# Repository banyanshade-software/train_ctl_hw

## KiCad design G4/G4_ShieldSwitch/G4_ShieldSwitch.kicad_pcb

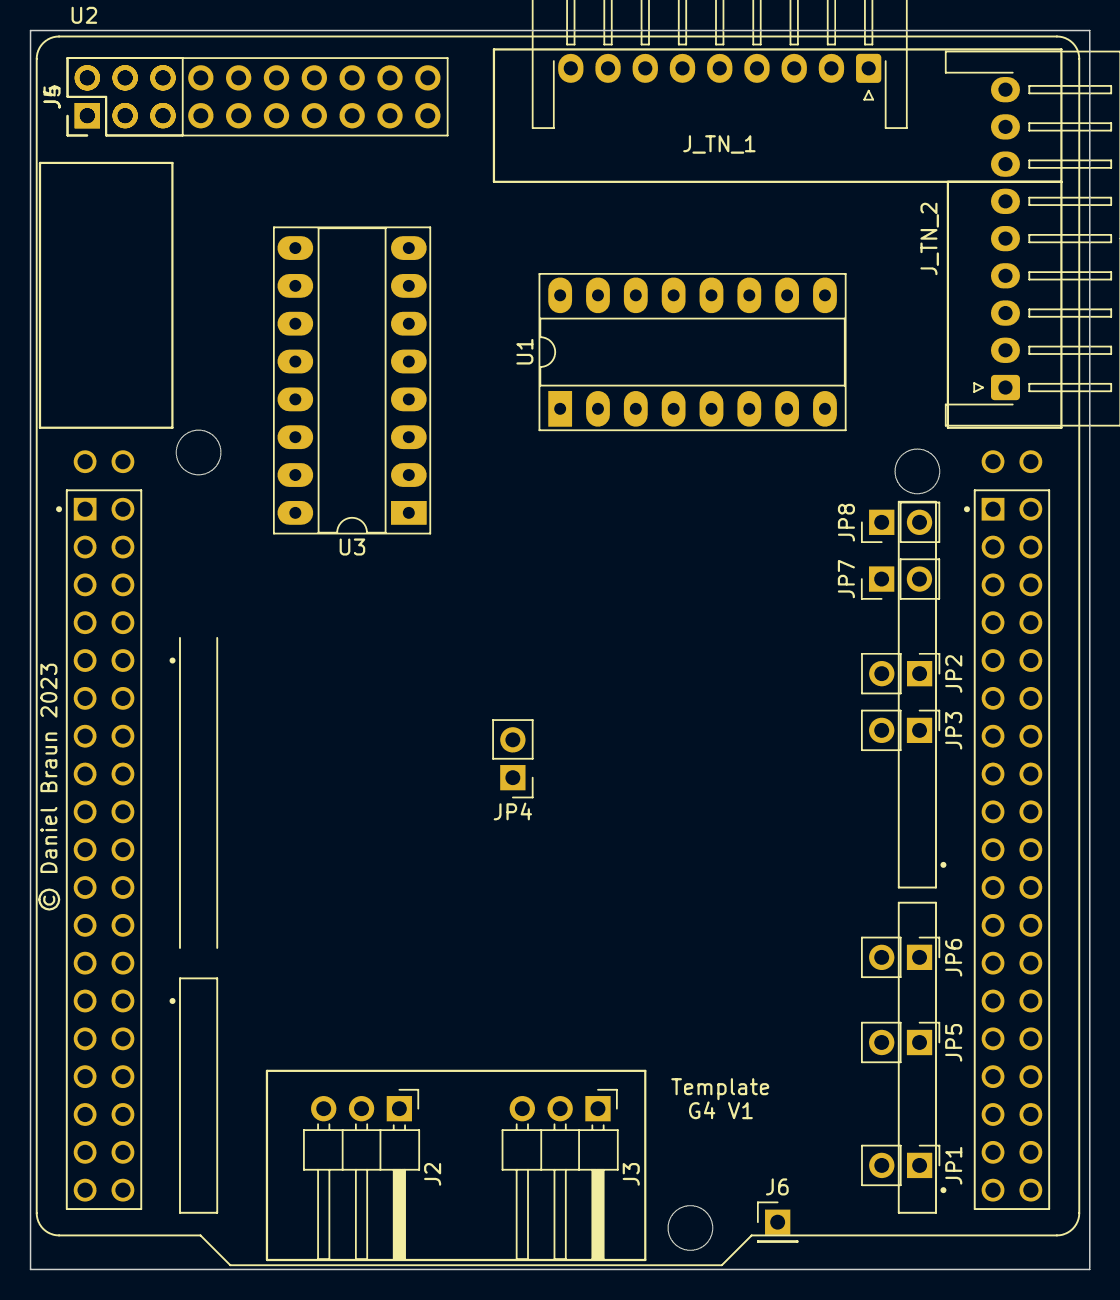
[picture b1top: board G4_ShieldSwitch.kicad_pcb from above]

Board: 2 copper layers, 71.1 x 83.2 mm, 18 parts (0 on the bottom side), 35 nets, no tracks yet.

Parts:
J2, J3: Conn_01x03_Male; PinHeader_1x03_P2.54mm_Horizontal
J4: Conn_02x10_Odd_Even; PinHeader_2x10_P2.54mm_Vertical
J5: Conn_02x03_Odd_Even; PinHeader_2x03_P2.54mm_Vertical
J6: Conn_01x01_Female; PinHeader_1x01_P2.54mm_Vertical
JP1, JP2, JP3, JP4, JP5, JP6, JP7, JP8: SJ; PinHeader_1x02_P2.54mm_Vertical
J_TN_1, J_TN_2: Conn_01x09_Female; JST_XH_S9B-XH-A-1_1x09_P2.50mm_Horizontal
U1, U3: ULN2003A; DIP-16_W7.62mm_Socket_LongPads
U2: NUCLEO-G491RE; MODULE_NUCLEO-G491RE20

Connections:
5V: J4.1, J5.1
12V: J4.5, J5.5
+12V: J_TN_1.2, J_TN_1.5, J_TN_1.8, J_TN_2.2, J_TN_2.5, J_TN_2.8, U1.9 (COM), U3.9 (COM)
ALED8: J_TN_1.7, U3.12 (O5)
ALED9: J_TN_1.9, U3.11 (O6)
GND: J4.3, J5.3, J6.1, U1.8 (GND), U2.CN7_8 (CN7_GND), U2.CN7_19 (CN7_GND), U2.CN7_20 (CN7_GND), U2.CN7_22 (CN7_GND), U2.CN10_9 (CN10_GND), U2.CN10_20 (CN10_GND), U3.8 (GND)
unnamed: J_TN_1.1, U3.16 (O1)
unnamed: J_TN_1.3, U3.15 (O2)
unnamed: J_TN_1.4, U3.14 (O3)
unnamed: J_TN_1.6, U3.13 (O4)
unnamed: J_TN_2.1, U1.16 (O1)
unnamed: J_TN_2.3, U1.15 (O2)
unnamed: J_TN_2.4, U1.14 (O3)
unnamed: J_TN_2.6, U1.13 (O4)
unnamed: J_TN_2.7, U1.12 (O5)
unnamed: J_TN_2.9, U1.11 (O6)
unnamed: JP8.2 (B), U2.CN10_1 (PC9)
unnamed: JP7.2 (B), U2.CN10_2 (PC8)
unnamed: JP2.1 (A), U2.CN10_11 (PA5)
unnamed: JP3.1 (A), U2.CN10_13 (PA6)
unnamed: JP6.1 (A), U2.CN10_25 (PB10)
unnamed: JP5.1 (A), U2.CN10_29 (PB5)
unnamed: JP1.1 (A), U2.CN10_37 (PA3)
TN0A: U1.1 (I1), U2.CN10_3 (PB8/CAN1RX)
TN0B: U1.2 (I2), U2.CN10_6 (PC5)
TN1A: U1.3 (I3), U2.CN10_19 (PC7)
TN1B: U1.4 (I4), U2.CN10_28 (PB14)
TN2A: JP1.2 (B), JP7.1 (A), U1.5 (I5)
TN2B: U1.6 (I6), U2.CN10_34 (PC4)
TN3A: JP4.2 (B), U3.1 (I1)
TN3B: JP6.2 (B), U3.2 (I2)
TN4A: JP8.1 (A), U3.3 (I3)
TN4B: JP2.2 (B), U3.4 (I4)
TN5A: JP3.2 (B), U3.5 (I5)
TN5B: JP5.2 (B), U3.6 (I6)

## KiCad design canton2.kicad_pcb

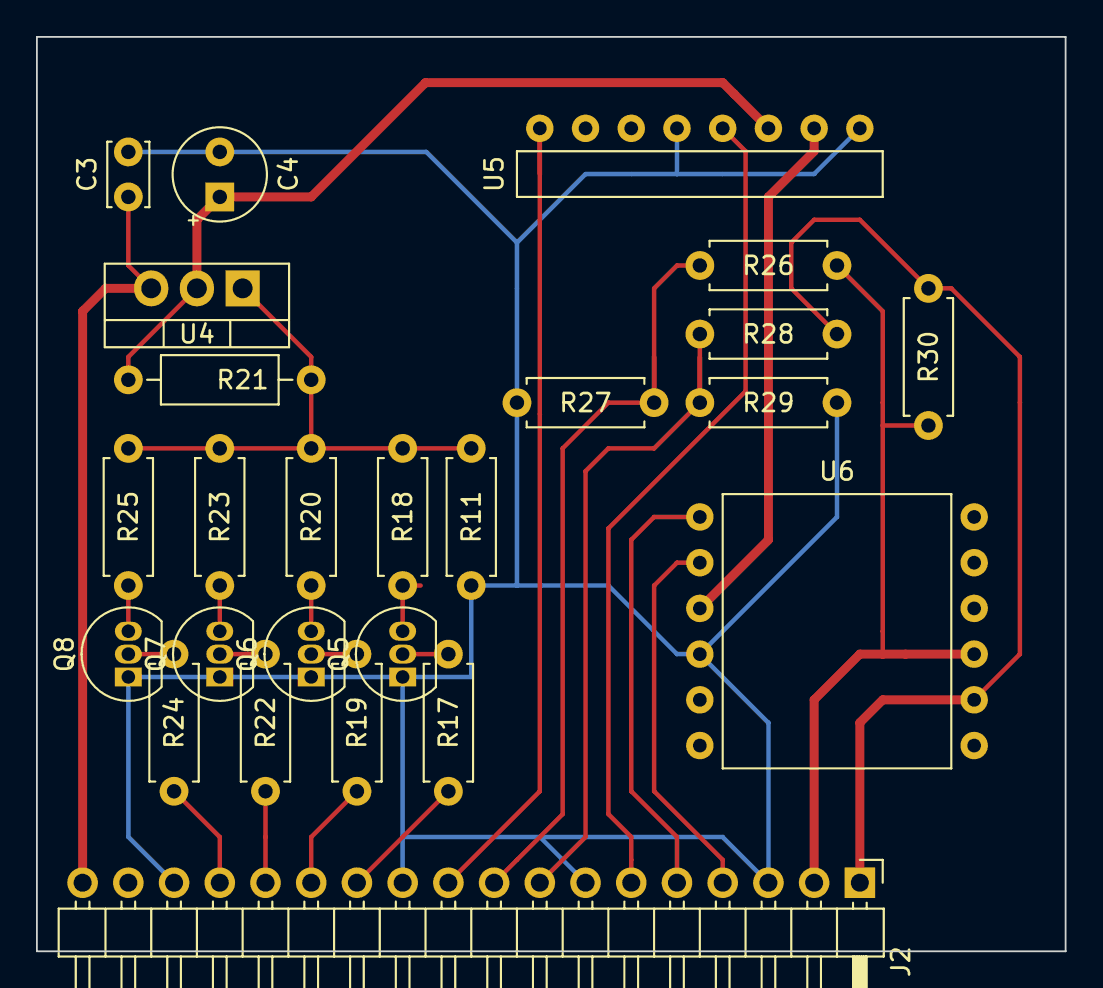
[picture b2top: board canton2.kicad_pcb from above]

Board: 2 copper layers, 57.2 x 50.8 mm, 25 parts (0 on the bottom side), 25 nets.

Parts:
C3: 0.1µF; C_Disc_D3.4mm_W2.1mm_P2.50mm
C4: 10µF; CP_Radial_Tantal_D5.0mm_P2.50mm
J2: Conn_01x18; PinHeader_1x18_P2.54mm_Horizontal
Q5, Q6, Q7, Q8: PN2222A; TO-92_Inline
R11, R18, R20, R23, R25: R; R_Axial_DIN0207_L6.3mm_D2.5mm_P7.62mm_Horizontal
R17, R19, R22, R24, R27, R29: 2200; R_Axial_DIN0207_L6.3mm_D2.5mm_P7.62mm_Horizontal
R21: 240; R_Axial_DIN0207_L6.3mm_D2.5mm_P10.16mm_Horizontal
R26, R28: 10k; R_Axial_DIN0207_L6.3mm_D2.5mm_P7.62mm_Horizontal
R30: 3k; R_Axial_DIN0207_L6.3mm_D2.5mm_P7.62mm_Horizontal
U4: LM317_TO220; TO-220-3_Vertical
U5: CJMCU-4080; module_1x8
U6: ModuleDRV8833; module_2x6

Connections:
3.3V: J2.6, U5.4
12Vunreg: C3.1, J2.18, U4.3
CT0: J2.12, R17.2
CT1: J2.13, R19.2
CT2: J2.14, R22.2
CT3: J2.15, R24.2
GND: C3.2, C4.2, J2.3, J2.7, J2.11, J2.16, Q5.1, Q6.1, Q7.1, Q8.1, R11.2, R27.2, R29.2, U5.1, U5.5, U6.10
ISENSE: J2.10, U5.8
unnamed: C4.1, R21.1, U4.2, U5.3
unnamed: Q5.2, R17.1
unnamed: Q5.3, R18.2
unnamed: Q6.2, R19.1
unnamed: Q6.3, R20.2
unnamed: Q7.2, R22.1
unnamed: Q7.3, R23.2
unnamed: Q8.2, R24.1
unnamed: Q8.3, R25.2
unnamed: R11.1, R18.1, R20.1, R21.2, R23.1, R25.1, U4.1
unnamed: U5.2, U6.9
PWM1: J2.5, U6.7
PWM2: J2.4, U6.8
TRACK0: J2.1, R28.1, R30.1, U6.2
TRACK1: J2.2, R26.1, R30.2, U6.3
VSENSE0: J2.9, R26.2, R27.1
VSENSE1: J2.8, R28.2, R29.1

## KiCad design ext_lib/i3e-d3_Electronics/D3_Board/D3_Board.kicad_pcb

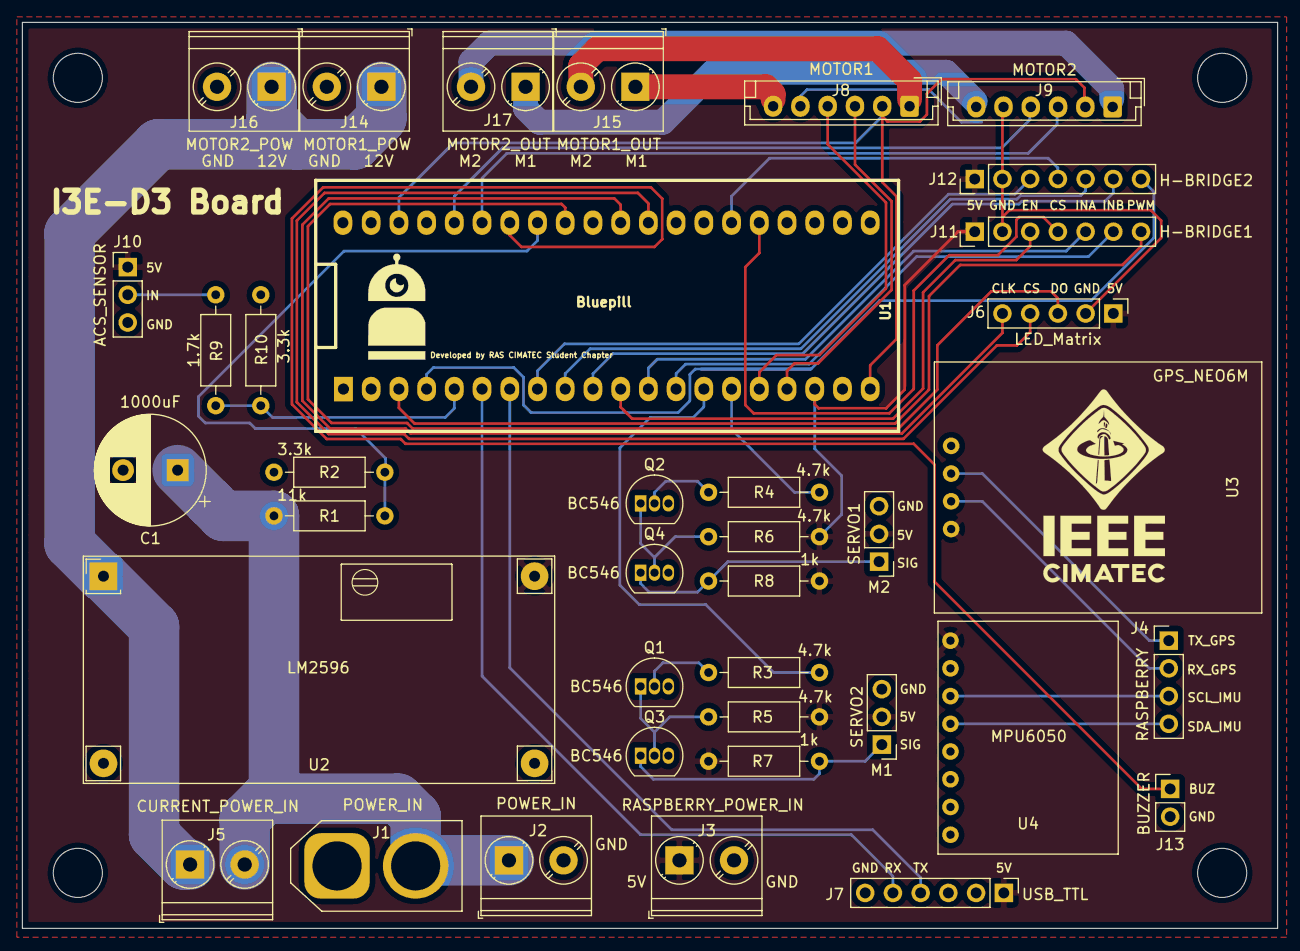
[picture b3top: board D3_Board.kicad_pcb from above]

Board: 2 copper layers, 115.0 x 83.0 mm, 38 parts (0 on the bottom side), 44 nets.

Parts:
C1: 1000uF; CP_Radial_D10.0mm_P5.00mm
J1: POWER_IN; AMASS_XT60-M_1x02_P7.20mm_Vertical
J2: POWER_IN; TerminalBlock_Phoenix_PT-1,5-2-5.0-H_1x02_P5.00mm_Horizontal
J3: RASPBERRY_POWER_IN; TerminalBlock_Phoenix_PT-1,5-2-5.0-H_1x02_P5.00mm_Horizontal
J4: RASPBERRY; PinHeader_1x04_P2.54mm_Vertical
J5: CURRENT_POWER_IN; TerminalBlock_Phoenix_PT-1,5-2-5.0-H_1x02_P5.00mm_Horizontal
J6: LED_Matrix; PinHeader_1x05_P2.54mm_Vertical
J7: USB_TTL; PinHeader_1x06_P2.54mm_Vertical
J8: MOTOR1; JST_EH_B6B-EH-A_1x06_P2.50mm_Vertical
J9: MOTOR2; JST_EH_B6B-EH-A_1x06_P2.50mm_Vertical
J10: ACS_SENSOR; PinHeader_1x03_P2.54mm_Vertical
J11: H-BRIDGE1; PinHeader_1x07_P2.54mm_Vertical
J12: H-BRIDGE2; PinHeader_1x07_P2.54mm_Vertical
J13: BUZZER; PinHeader_1x02_P2.54mm_Vertical
J14: MOTOR1_POW; TerminalBlock_Phoenix_PT-1,5-2-5.0-H_1x02_P5.00mm_Horizontal
J15: MOTOR1_OUT; TerminalBlock_Phoenix_PT-1,5-2-5.0-H_1x02_P5.00mm_Horizontal
J16: MOTOR2_POW; TerminalBlock_Phoenix_PT-1,5-2-5.0-H_1x02_P5.00mm_Horizontal
J17: MOTOR2_OUT; TerminalBlock_Phoenix_PT-1,5-2-5.0-H_1x02_P5.00mm_Horizontal
M1: SERVO2; PinHeader_1x03_P2.54mm_Vertical
M2: SERVO1; PinHeader_1x03_P2.54mm_Vertical
Q1, Q2, Q3, Q4: BC546; TO-92_Inline
R1: 11k; R_Axial_DIN0207_L6.3mm_D2.5mm_P10.16mm_Horizontal
R2, R10: 3.3k; R_Axial_DIN0207_L6.3mm_D2.5mm_P10.16mm_Horizontal
R3, R4, R5, R6: 4.7k; R_Axial_DIN0207_L6.3mm_D2.5mm_P10.16mm_Horizontal
R7, R8: 1k; R_Axial_DIN0207_L6.3mm_D2.5mm_P10.16mm_Horizontal
R9: 1.7k; R_Axial_DIN0207_L6.3mm_D2.5mm_P10.16mm_Horizontal
U1: Bluepill; BluePill_STM32F103C
U2: LM2596; LM2596_module
U3: GPS_NEO6M; GPS_NEO6M_module
U4: MPU6050; MPU6050_module

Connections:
+3V3: J8.2, J9.2, U1.20, U1.38
+5V: J3.1, J6.1, J7.1, J10.1, J11.1, J12.1, M1.2, M2.2, R5.2, R6.2, R7.2, R8.2, U1.18, U2.4, U3.1, U4.1
+12V: J5.1, J14.1, J16.1, U2.1
/ACS: R9.2, R10.1, U1.5
/AVS: R1.2, R2.1, U1.33
/BUZZER: J13.1, U1.34
/CLK_LED: J6.5, U1.30
/CS_LED: J6.4, U1.29
/DOUT_LED: J6.3, U1.32
/ENCODER1_A: J8.4, U1.16
/ENCODER1_B: J8.3, U1.17
/ENCODER2_A: J9.4, U1.36
/ENCODER2_B: J9.3, U1.35
/MOTOR1_CS: J11.4, U1.25
/MOTOR1_EN: J11.3, U1.11
/MOTOR1_INA: J11.5, U1.12
/MOTOR1_INB: J11.6, U1.13
/MOTOR1_M1: J8.6, J15.1
/MOTOR1_M2: J8.1, J15.2
/MOTOR1_PWM: J11.7, U1.3
/MOTOR2_CS: J12.4, U1.26
/MOTOR2_EN: J12.3, U1.8
/MOTOR2_INA: J12.5, U1.9
/MOTOR2_INB: J12.6, U1.10
/MOTOR2_M1: J9.6, J17.1
/MOTOR2_M2: J9.1, J17.2
/MOTOR2_PWM: J12.7, U1.4
/RX_GPS: J4.2, U3.2
/RX_SERIAL: J7.5, U1.6
/SCL: J4.3, U4.3
/SDA: J4.4, U4.4
/SERVO1: R3.2, U1.14
/SERVO2: R4.2, U1.15
/TX_GPS: J4.1, U3.3
/TX_SERIAL: J7.4, U1.7
GND: C1.2, J1.1, J2.2, J3.2, J6.2, J7.6, J8.5, J9.5, J10.3, J11.2, J12.2, J13.2, J14.2, J16.2, M1.3, M2.3, Q1.3, Q2.3, Q3.3, Q4.3, R2.2, R10.2, U1.19, U1.39, U1.40, U2.2, U2.3, U3.4, U4.2
unnamed: C1.1, J1.2, J2.1, J5.2, R1.1
unnamed: J10.2, R9.1
unnamed: M1.1, Q3.1, R7.1
unnamed: M2.1, Q4.1, R8.1
unnamed: Q1.1, Q3.2, R5.1
unnamed: Q1.2, R3.1
unnamed: Q2.1, Q4.2, R6.1
unnamed: Q2.2, R4.1

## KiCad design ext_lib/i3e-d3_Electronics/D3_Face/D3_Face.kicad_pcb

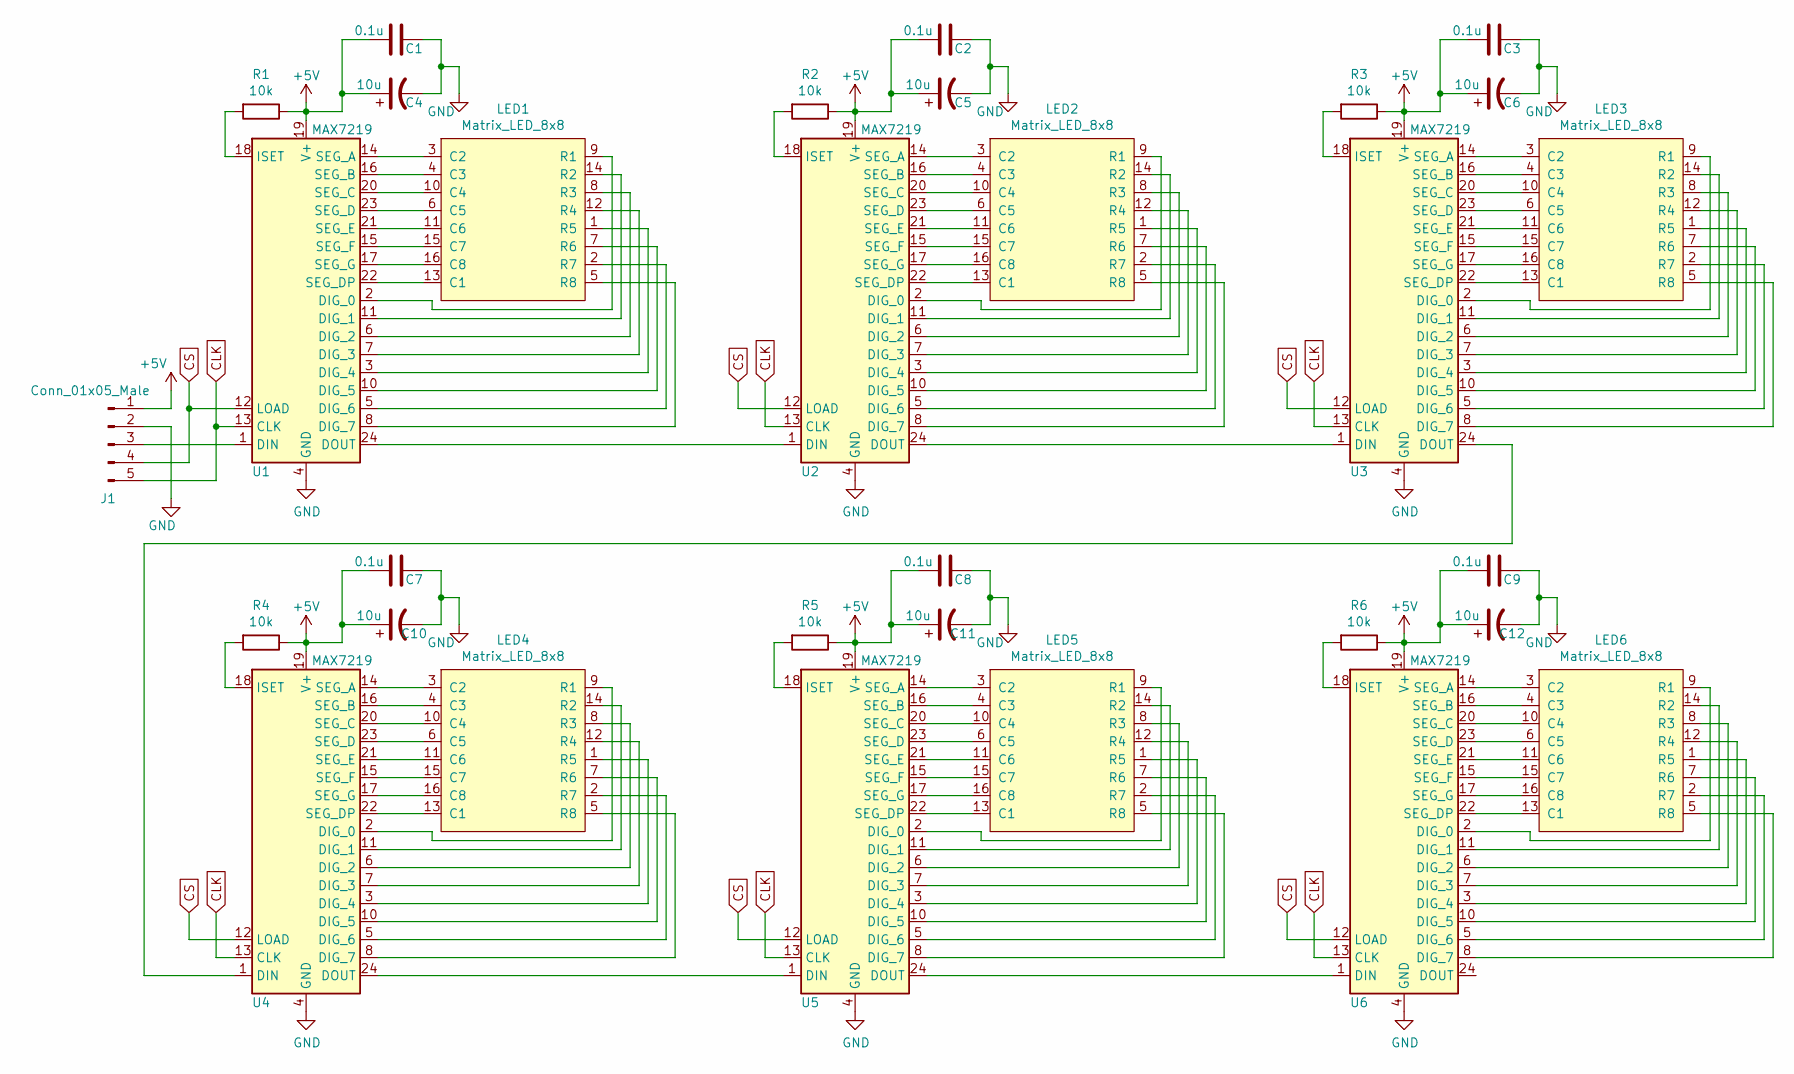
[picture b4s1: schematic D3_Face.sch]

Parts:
C1, C2, C3, C7, C8, C9: 0.1u; C_Disc_D4.3mm_W1.9mm_P5.00mm
C4, C5, C6, C10, C11, C12: 10u; CP_Radial_D4.0mm_P2.00mm
J1: Conn_01x05_Male; PinHeader_1x05_P2.54mm_Horizontal
LED1, LED2, LED3, LED4, LED5, LED6: Matrix_LED_8x8
R1, R2, R3, R4, R5, R6: 10k; R_Axial_DIN0207_L6.3mm_D2.5mm_P10.16mm_Horizontal
U1, U2, U3, U4, U5, U6: MAX7219; DIP-24_W7.62mm_Socket_LongPads

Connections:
+5V: C1.2, C2.2, C3.2, C4.1, C5.1, C6.1, C7.2, C8.2, C9.2, C10.1, C11.1, C12.1, J1.1, R1.1, R2.1, R3.1, R4.1, R5.1, R6.1, U1.19 (V+), U2.19 (V+), U3.19 (V+), U4.19 (V+), U5.19 (V+), U6.19 (V+)
CLK: J1.5, U1.13 (CLK), U2.13 (CLK), U3.13 (CLK), U4.13 (CLK), U5.13 (CLK), U6.13 (CLK)
CS: J1.4, U1.12 (LOAD), U2.12 (LOAD), U3.12 (LOAD), U4.12 (LOAD), U5.12 (LOAD), U6.12 (LOAD)
GND: C1.1, C2.1, C3.1, C4.2, C5.2, C6.2, C7.1, C8.1, C9.1, C10.2, C11.2, C12.2, J1.2, U1.4 (GND), U1.9 (GND), U2.4 (GND), U2.9 (GND), U3.4 (GND), U3.9 (GND), U4.4 (GND), U4.9 (GND), U5.4 (GND), U5.9 (GND), U6.4 (GND), U6.9 (GND)
unnamed: J1.3, U1.1 (DIN)
unnamed: LED1.1 (R5), U1.3 (DIG_4)
unnamed: LED1.2 (R7), U1.5 (DIG_6)
unnamed: LED1.3 (C2), U1.14 (SEG_A)
unnamed: LED1.4 (C3), U1.16 (SEG_B)
unnamed: LED1.5 (R8), U1.8 (DIG_7)
unnamed: LED1.6 (C5), U1.23 (SEG_D)
unnamed: LED1.7 (R6), U1.10 (DIG_5)
unnamed: LED1.8 (R3), U1.6 (DIG_2)
unnamed: LED1.9 (R1), U1.2 (DIG_0)
unnamed: LED1.10 (C4), U1.20 (SEG_C)
unnamed: LED1.11 (C6), U1.21 (SEG_E)
unnamed: LED1.12 (R4), U1.7 (DIG_3)
unnamed: LED1.13 (C1), U1.22 (SEG_DP)
unnamed: LED1.14 (R2), U1.11 (DIG_1)
unnamed: LED1.15 (C7), U1.15 (SEG_F)
unnamed: LED1.16 (C8), U1.17 (SEG_G)
unnamed: LED2.1 (R5), U2.3 (DIG_4)
unnamed: LED2.2 (R7), U2.5 (DIG_6)
unnamed: LED2.3 (C2), U2.14 (SEG_A)
unnamed: LED2.4 (C3), U2.16 (SEG_B)
unnamed: LED2.5 (R8), U2.8 (DIG_7)
unnamed: LED2.6 (C5), U2.23 (SEG_D)
unnamed: LED2.7 (R6), U2.10 (DIG_5)
unnamed: LED2.8 (R3), U2.6 (DIG_2)
unnamed: LED2.9 (R1), U2.2 (DIG_0)
unnamed: LED2.10 (C4), U2.20 (SEG_C)
unnamed: LED2.11 (C6), U2.21 (SEG_E)
unnamed: LED2.12 (R4), U2.7 (DIG_3)
unnamed: LED2.13 (C1), U2.22 (SEG_DP)
unnamed: LED2.14 (R2), U2.11 (DIG_1)
unnamed: LED2.15 (C7), U2.15 (SEG_F)
unnamed: LED2.16 (C8), U2.17 (SEG_G)
unnamed: LED3.1 (R5), U3.3 (DIG_4)
unnamed: LED3.2 (R7), U3.5 (DIG_6)
unnamed: LED3.3 (C2), U3.14 (SEG_A)
unnamed: LED3.4 (C3), U3.16 (SEG_B)
unnamed: LED3.5 (R8), U3.8 (DIG_7)
unnamed: LED3.6 (C5), U3.23 (SEG_D)
unnamed: LED3.7 (R6), U3.10 (DIG_5)
unnamed: LED3.8 (R3), U3.6 (DIG_2)
unnamed: LED3.9 (R1), U3.2 (DIG_0)
unnamed: LED3.10 (C4), U3.20 (SEG_C)
unnamed: LED3.11 (C6), U3.21 (SEG_E)
unnamed: LED3.12 (R4), U3.7 (DIG_3)
unnamed: LED3.13 (C1), U3.22 (SEG_DP)
unnamed: LED3.14 (R2), U3.11 (DIG_1)
unnamed: LED3.15 (C7), U3.15 (SEG_F)
unnamed: LED3.16 (C8), U3.17 (SEG_G)
unnamed: LED4.1 (R5), U4.3 (DIG_4)
unnamed: LED4.2 (R7), U4.5 (DIG_6)
unnamed: LED4.3 (C2), U4.14 (SEG_A)
unnamed: LED4.4 (C3), U4.16 (SEG_B)
unnamed: LED4.5 (R8), U4.8 (DIG_7)
unnamed: LED4.6 (C5), U4.23 (SEG_D)
unnamed: LED4.7 (R6), U4.10 (DIG_5)
unnamed: LED4.8 (R3), U4.6 (DIG_2)
unnamed: LED4.9 (R1), U4.2 (DIG_0)
unnamed: LED4.10 (C4), U4.20 (SEG_C)
unnamed: LED4.11 (C6), U4.21 (SEG_E)
unnamed: LED4.12 (R4), U4.7 (DIG_3)
unnamed: LED4.13 (C1), U4.22 (SEG_DP)
unnamed: LED4.14 (R2), U4.11 (DIG_1)
unnamed: LED4.15 (C7), U4.15 (SEG_F)
unnamed: LED4.16 (C8), U4.17 (SEG_G)
unnamed: LED5.1 (R5), U5.3 (DIG_4)
unnamed: LED5.2 (R7), U5.5 (DIG_6)
unnamed: LED5.3 (C2), U5.14 (SEG_A)
unnamed: LED5.4 (C3), U5.16 (SEG_B)
unnamed: LED5.5 (R8), U5.8 (DIG_7)
unnamed: LED5.6 (C5), U5.23 (SEG_D)
unnamed: LED5.7 (R6), U5.10 (DIG_5)
unnamed: LED5.8 (R3), U5.6 (DIG_2)
unnamed: LED5.9 (R1), U5.2 (DIG_0)
unnamed: LED5.10 (C4), U5.20 (SEG_C)
unnamed: LED5.11 (C6), U5.21 (SEG_E)
unnamed: LED5.12 (R4), U5.7 (DIG_3)
unnamed: LED5.13 (C1), U5.22 (SEG_DP)
unnamed: LED5.14 (R2), U5.11 (DIG_1)
unnamed: LED5.15 (C7), U5.15 (SEG_F)
unnamed: LED5.16 (C8), U5.17 (SEG_G)
unnamed: LED6.1 (R5), U6.3 (DIG_4)
unnamed: LED6.2 (R7), U6.5 (DIG_6)
unnamed: LED6.3 (C2), U6.14 (SEG_A)
unnamed: LED6.4 (C3), U6.16 (SEG_B)
unnamed: LED6.5 (R8), U6.8 (DIG_7)
unnamed: LED6.6 (C5), U6.23 (SEG_D)
unnamed: LED6.7 (R6), U6.10 (DIG_5)
unnamed: LED6.8 (R3), U6.6 (DIG_2)
unnamed: LED6.9 (R1), U6.2 (DIG_0)
unnamed: LED6.10 (C4), U6.20 (SEG_C)
unnamed: LED6.11 (C6), U6.21 (SEG_E)
unnamed: LED6.12 (R4), U6.7 (DIG_3)
unnamed: LED6.13 (C1), U6.22 (SEG_DP)
unnamed: LED6.14 (R2), U6.11 (DIG_1)
unnamed: LED6.15 (C7), U6.15 (SEG_F)
unnamed: LED6.16 (C8), U6.17 (SEG_G)
unnamed: R1.2, U1.18 (ISET)
unnamed: R2.2, U2.18 (ISET)
unnamed: R3.2, U3.18 (ISET)
unnamed: R4.2, U4.18 (ISET)
unnamed: R5.2, U5.18 (ISET)
unnamed: R6.2, U6.18 (ISET)
unnamed: U1.24 (DOUT), U2.1 (DIN)
unnamed: U2.24 (DOUT), U3.1 (DIN)
unnamed: U3.24 (DOUT), U4.1 (DIN)
unnamed: U4.24 (DOUT), U5.1 (DIN)
unnamed: U5.24 (DOUT), U6.1 (DIN)

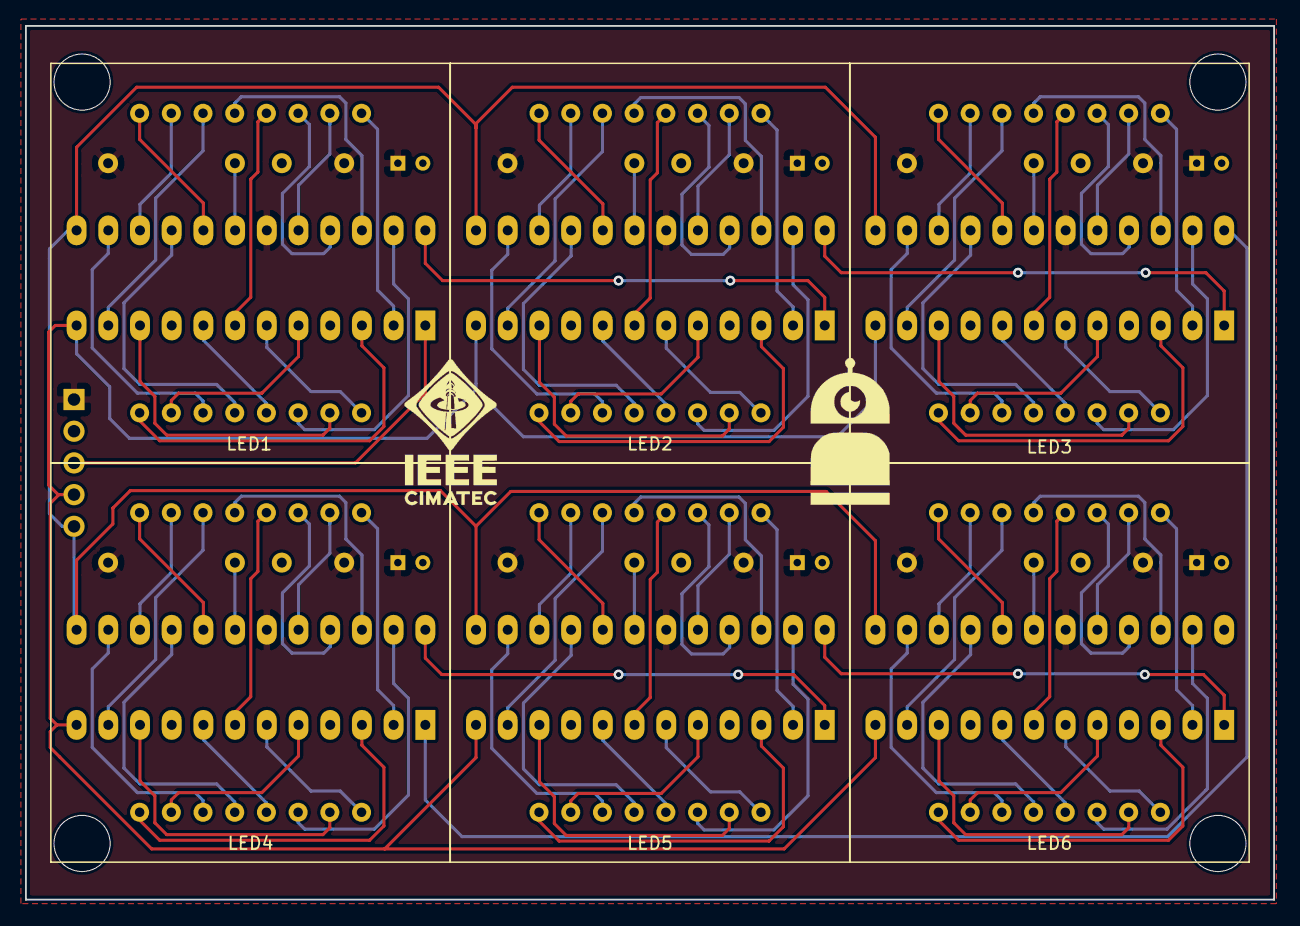
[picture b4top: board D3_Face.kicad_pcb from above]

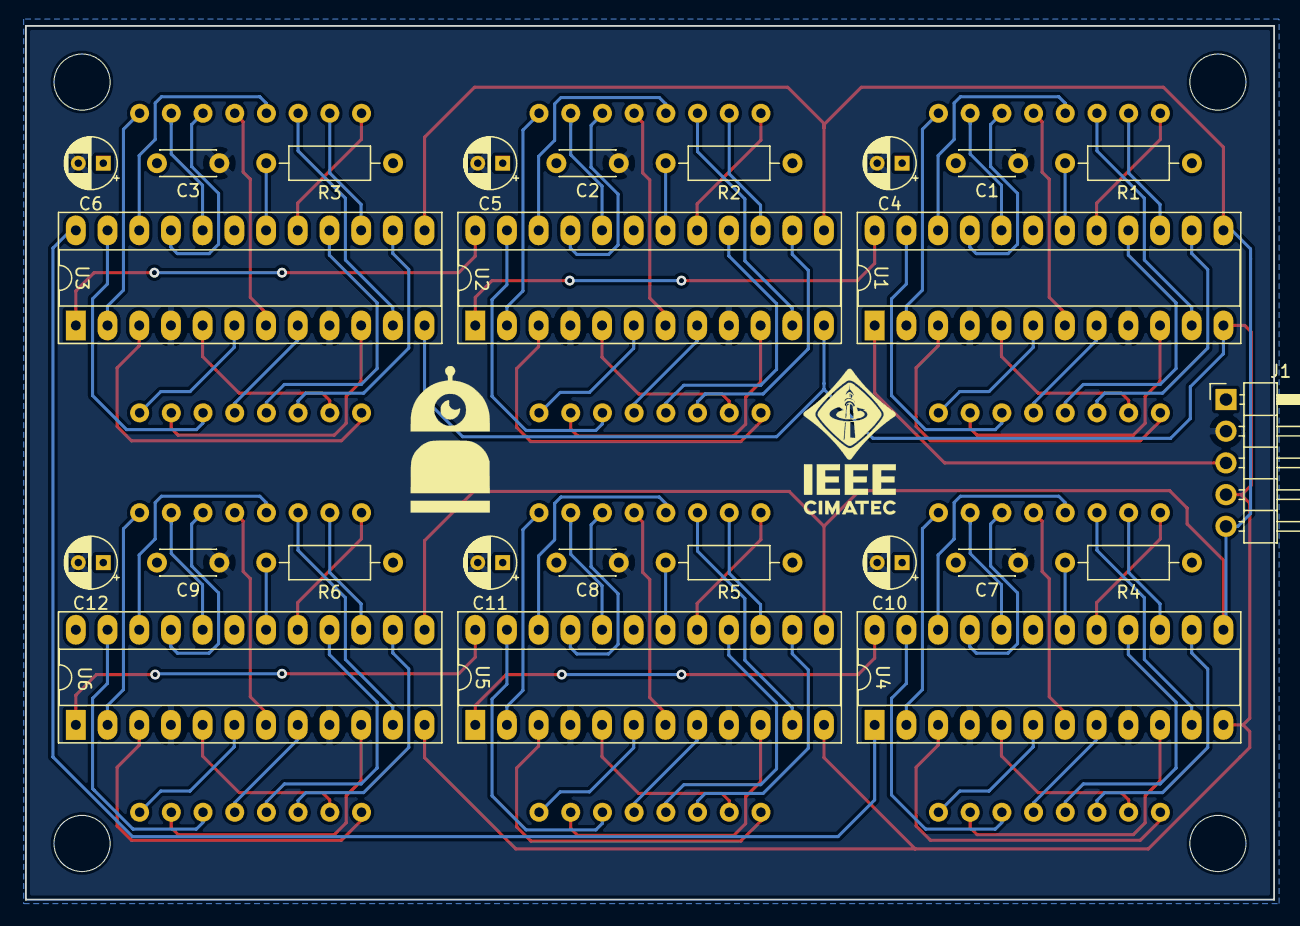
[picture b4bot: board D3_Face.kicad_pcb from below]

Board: 2 copper layers, 100.0 x 70.0 mm, 31 parts (25 on the bottom side), 112 nets.

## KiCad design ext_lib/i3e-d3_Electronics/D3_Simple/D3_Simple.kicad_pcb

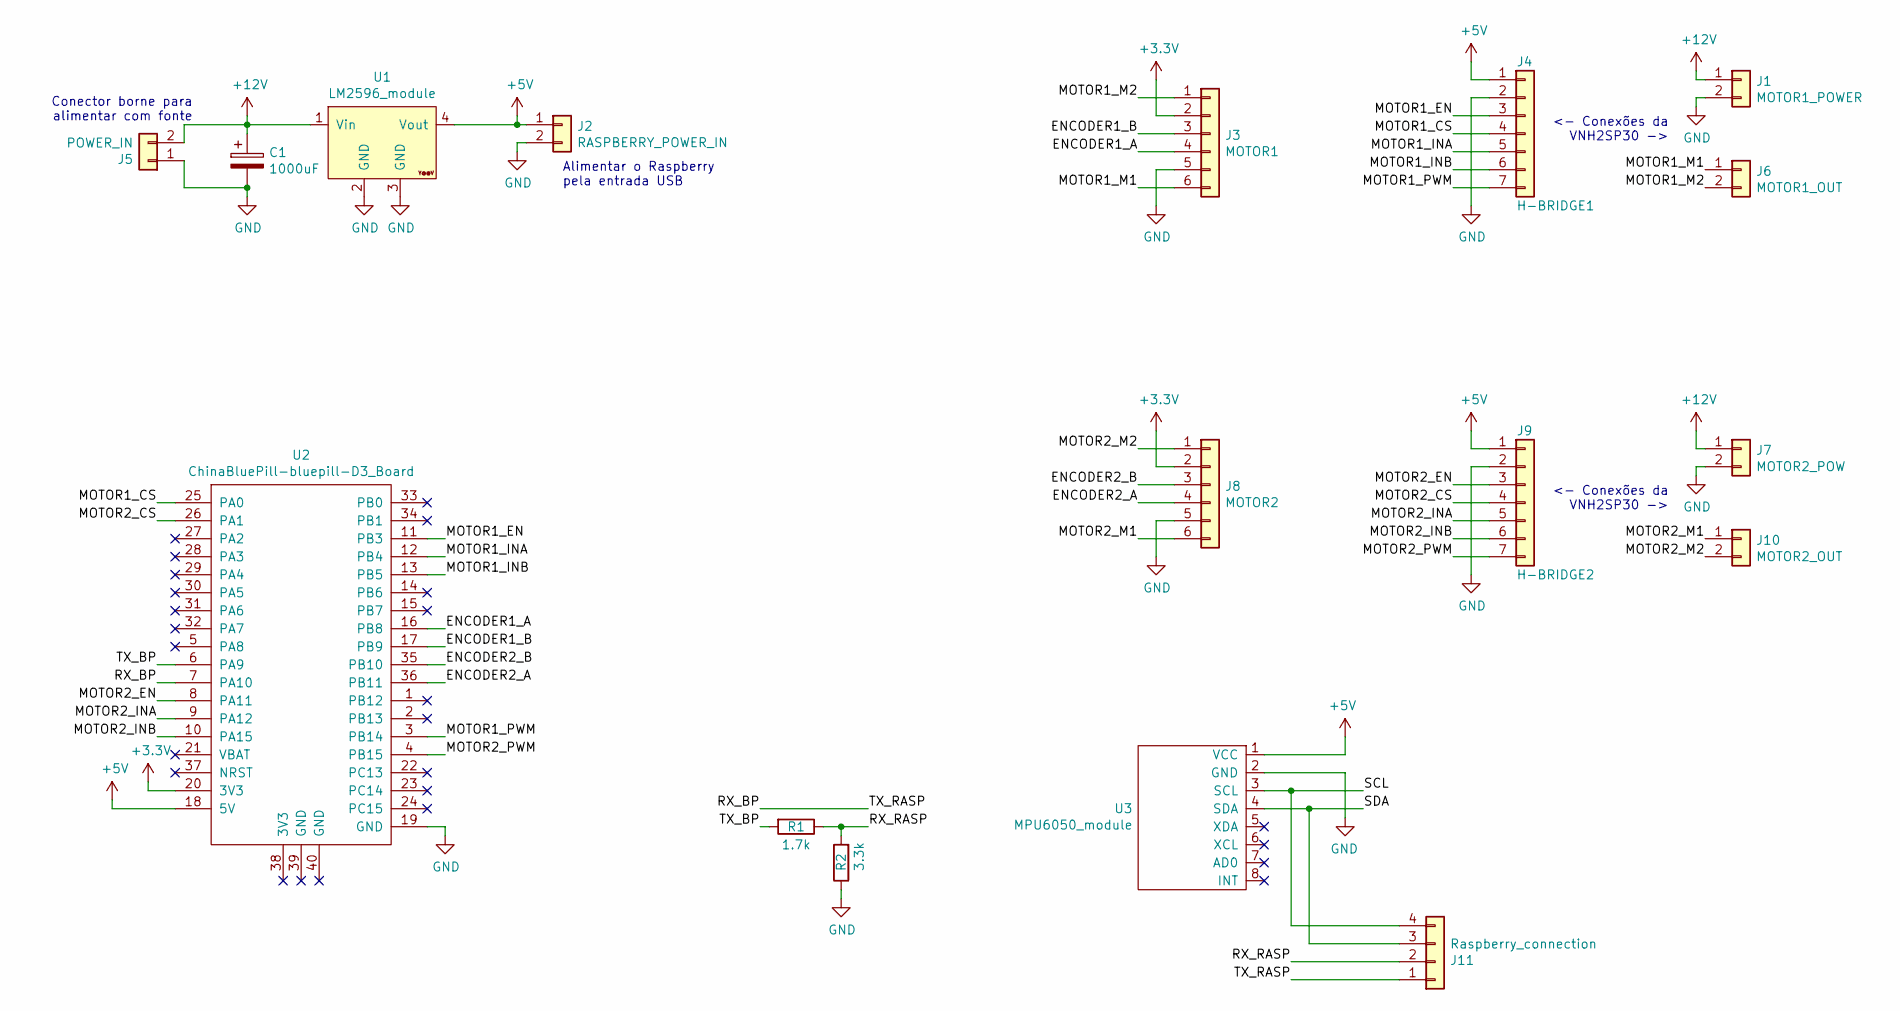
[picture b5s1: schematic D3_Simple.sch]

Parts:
C1: 1000uF; CP_Radial_D10.0mm_P5.00mm
J1: MOTOR1_POWER; TerminalBlock_Phoenix_PT-1,5-2-5.0-H_1x02_P5.00mm_Horizontal
J2: RASPBERRY_POWER_IN; TerminalBlock_Phoenix_PT-1,5-2-5.0-H_1x02_P5.00mm_Horizontal
J3: MOTOR1; JST_EH_B6B-EH-A_1x06_P2.50mm_Vertical
J4: H-BRIDGE1; PinHeader_1x07_P2.54mm_Vertical
J5: POWER_IN; TerminalBlock_Phoenix_PT-1,5-2-5.0-H_1x02_P5.00mm_Horizontal
J6: MOTOR1_OUT; TerminalBlock_Phoenix_PT-1,5-2-5.0-H_1x02_P5.00mm_Horizontal
J7: MOTOR2_POW; TerminalBlock_Phoenix_PT-1,5-2-5.0-H_1x02_P5.00mm_Horizontal
J8: MOTOR2; JST_EH_B6B-EH-A_1x06_P2.50mm_Vertical
J9: H-BRIDGE2; PinHeader_1x07_P2.54mm_Vertical
J10: MOTOR2_OUT; TerminalBlock_Phoenix_PT-1,5-2-5.0-H_1x02_P5.00mm_Horizontal
J11: Raspberry_connection; PinHeader_1x04_P2.54mm_Vertical
R1: 1.7k; R_Axial_DIN0207_L6.3mm_D2.5mm_P10.16mm_Horizontal
R2: 3.3k; R_Axial_DIN0207_L6.3mm_D2.5mm_P10.16mm_Horizontal
U1: LM2596_module
U2: ChinaBluePill-bluepill-D3_Board; BluePill_STM32F103C
U3: MPU6050_module

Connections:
+3V3: J3.2, J8.2, U2.20 (3V3)
+5V: J2.1, J4.1, J9.1, U1.4 (Vout), U2.18 (5V), U3.1 (VCC)
+12V: C1.1, J1.1, J5.2, J7.1, U1.1 (Vin)
/ENCODER1_A: J3.4, U2.16 (PB8)
/ENCODER1_B: J3.3, U2.17 (PB9)
/ENCODER2_A: J8.4, U2.36 (PB11)
/ENCODER2_B: J8.3, U2.35 (PB10)
/MOTOR1_CS: J4.4, U2.25 (PA0)
/MOTOR1_EN: J4.3, U2.11 (PB3)
/MOTOR1_INA: J4.5, U2.12 (PB4)
/MOTOR1_INB: J4.6, U2.13 (PB5)
/MOTOR1_M1: J3.6, J6.1
/MOTOR1_M2: J3.1, J6.2
/MOTOR1_PWM: J4.7, U2.3 (PB14)
/MOTOR2_CS: J9.4, U2.26 (PA1)
/MOTOR2_EN: J9.3, U2.8 (PA11)
/MOTOR2_INA: J9.5, U2.9 (PA12)
/MOTOR2_INB: J9.6, U2.10 (PA15)
/MOTOR2_M1: J8.6, J10.1
/MOTOR2_M2: J8.1, J10.2
/MOTOR2_PWM: J9.7, U2.4 (PB15)
/RX_BP: J11.1, U2.7 (PA10)
/RX_RASP: J11.2, R1.1, R2.2
/SCL: J11.4, U3.3 (SCL)
/SDA: J11.3, U3.4 (SDA)
/TX_BP: R1.2, U2.6 (PA9)
GND: C1.2, J1.2, J2.2, J3.5, J4.2, J5.1, J7.2, J8.5, J9.2, R2.1, U1.2 (GND), U1.3 (GND), U2.19 (GND), U3.2 (GND)

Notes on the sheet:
Alimentar o Raspberry pela entrada USB
Conector borne para alimentar com fonte
<- Conexões da VNH2SP30 ->

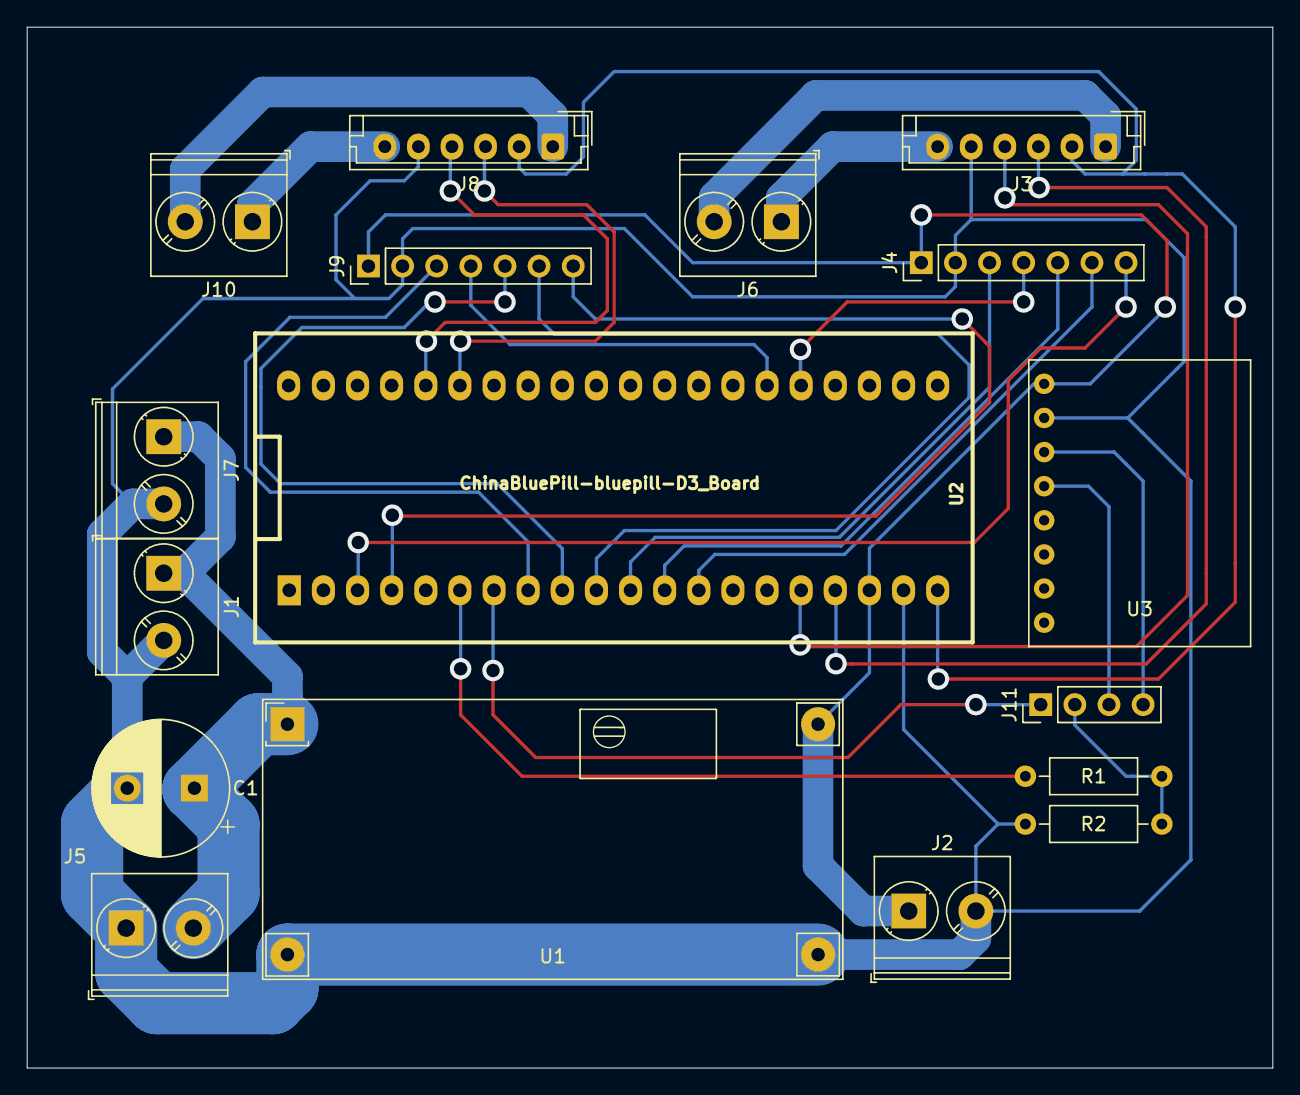
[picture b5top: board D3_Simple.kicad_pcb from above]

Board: 2 copper layers, 92.7 x 77.5 mm, 17 parts (0 on the bottom side), 27 nets.

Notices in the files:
G4/G4_ShieldSwitch/G4_ShieldSwitch.kicad_pcb:
© Daniel Braun 2023
